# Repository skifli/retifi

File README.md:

# Retifi

- [Retifi](#retifi)
  - [Journal](#journal)
  - [PCB](#pcb)
    - [Schematic](#schematic)
    - [PCB Design](#pcb-design)
  - [BOM](#bom)

A simple reaction time tester consisting of a main module, and two handheld parts (with a push-button each), and a lil screen (the blank area will be covered by various stickers from different Hackclub YSWSs I have participate in - mainly Sprig lol).

I made this because I compete in a competition called F1 in Schools (although its now been rebranded to STEM Racing, supported by F1), and as part of the competition our reaction times play a big role when launching the miniature F1 in Schools car down the track (side note you should totally check us out, we won the uk national finals last year in dev class, and are competing this year after exams - https://instagram.com/warp_racing_ and https://warp-racing.com).

Also sorry for this being a tad rushed with the images etc, I just lost a bunch of time because of GitHub Codespace being a pain ()

## Journal

Can be found in [`JOURNAL.md`](JOURNAL.md).

> [!NOTE]\
> Total time spent: **27h**

## PCB

### Schematic

### PCB Design

## BOM

In USD, $62.52.

<details closed>
<summary> Click to open (closed by default to save space lol)</summary>

| Component                | Description      | Notes                                                                                | Quantity | Price      | Shipping             | Provider               | Link                                                                                  |
| ------------------------ | ---------------- | ------------------------------------------------------------------------------------ | -------- | ---------- | -------------------- | ---------------------- | ------------------------------------------------------------------------------------- |
| Headers                  |                  | For screen because it doesn’t specify coming with some and I am taking zilch chances | 1        | £1.08      |                      | AliExpress             | [Link](https://www.aliexpress.com/item/4000988113226.html)                            |
| JST PH 2.00mm            | PH 2.00mm        | To connect the buttons to the PCB                                                    | 1        | £2.25      |                      |                        | [Link](https://www.aliexpress.com/item/1005007691949301.html)                         |
| Momentary Push Button    | Red 5PCS         | The actual button                                                                    | 1        | £3.23      |                      |                        | [Link](https://www.aliexpress.com/item/1005008498887267.html)                         |
| Heat Shrink Tube         | Mixed size       | Heat around the joint for the button to the switch                                   | 1        | £1.35      |                      |                        | [Link](https://www.aliexpress.com/item/1005008146302901.html)                         |
| Slide Switch             | k014a004-G3      | Switching it up here, eh? Lol ok that’s enough bad jokes for a day ;-;               | 1        | £2.09      |                      |                        | [Link](https://www.aliexpress.com/item/1005008904067609.html)                         |
| Nice nano                | But cheaaaper    | Teeheehee                                                                            | 1        | £2.21      |                      |                        | [Link](https://www.aliexpress.com/item/1005007383270623.html)                         |
| OLED                     | 2.42 I2C         |                                                                                      | 1        | £9.79      |                      |                        | [Link](https://www.aliexpress.com/item/1005008741364067.html)                         |
| Micro JST                | Male 5 Pcs 100mm | [Adafruit Guide](https://learn.adafruit.com/on-slash-off-switches/overview)          | 1        | £0.50      | £1.97                |                        | [Link](https://www.aliexpress.com/item/1005008864177105.html)                         |
| Micro JST                | Male 5 Pcs 100mm | [Adafruit Guide](https://learn.adafruit.com/on-slash-off-switches/overview)          | 1        | £0.34      | £1.97                |                        | [Link](https://www.aliexpress.com/item/1005008864177105.html)                         |
| Push Button              | 6x6x6mm          | For the reset function                                                               | 1        | £0.74      | £2.16                |                        | [Link](https://www.aliexpress.com/item/4001224103835.html)                            |
| **Total (AliExpress)**   |                  |                                                                                      |          | **£29.68** | Included on ze left! |                        |                                                                                       |
|                          |                  |                                                                                      |          |            |                      |                        |                                                                                       |
| 150mAh 3.7V LiPo Battery |                  | Couldn’t find any shipping sooner from AliExpress.                                   | 1        | £4.50      | £3.90                | PiHut                  | [Link](https://thepihut.com/products/150mah-3-7v-lipo-battery?variant=42388690993347) |
| **Total (PiHut)**        |                  |                                                                                      |          | **£8.40**  |                      |                        |                                                                                       |
|                          |                  |                                                                                      |          |            |                      |                        |                                                                                       |
| Comus Neodynium Magnet   | 3 by 4mm         | Again, AliExpress shipping is atrocious on this front.                               | 1        | £2.18      | £3.30 + £1.10 (VAT)  | Rapid Electronics (UK) | [Link](https://www.rapidonline.com/comus-m1219-3-neodynium-disc-magnet-78-1068)       |
|                          |                  |                                                                                      |          | **£6.58**  |                      |                        |                                                                                       |
|                          |                  |                                                                                      |          |            |                      |                        |                                                                                       |
| PCB                      |                  |                                                                                      | 1        | £1.51      | £1.13                | JLCPCB                 |                                                                                       |
|                          |                  |                                                                                      |          | **£2.64**  |                      |                        |                                                                                       |
|                          |                  |                                                                                      |          |            |                      |                        |                                                                                       |
| **TOTAL**                |                  |                                                                                      |          | **£47.30** |                      |                        |                                                                                       |

</details>

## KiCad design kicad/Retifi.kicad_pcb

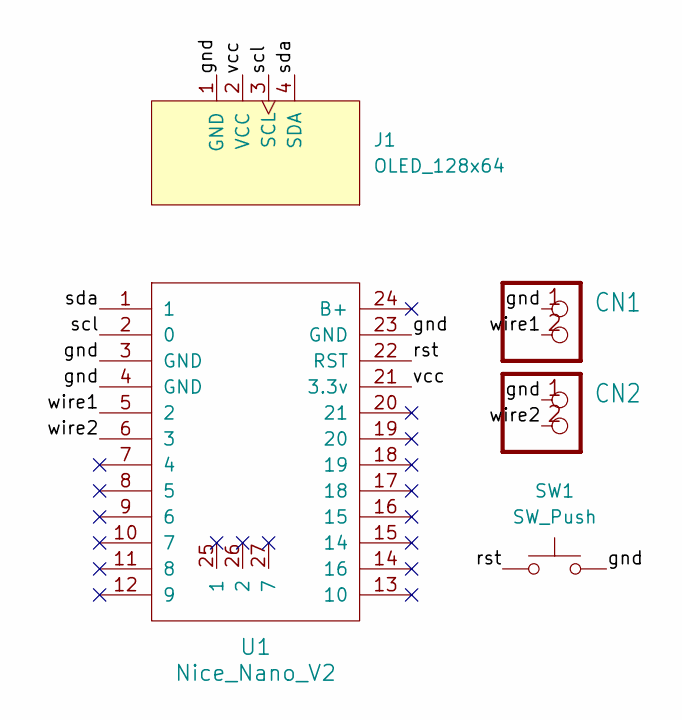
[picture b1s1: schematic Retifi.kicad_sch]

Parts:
CN1, CN2: JST_PH_S2B-PH-SM4-TB_1x02-1MP_P2.00mm_Horizontal
J1: OLED_128x64
SW1: SW_Push; Generic 2 Pin Horizontal
U1: Nice_Nano_V2

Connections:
/gnd: CN1.1, CN2.1, J1.1 (GND), SW1.2, U1.3 (GND), U1.4 (GND), U1.23 (GND)
/rst: SW1.1, U1.22 (RST)
/scl: J1.3 (SCL), U1.2 (0)
/sda: J1.4 (SDA), U1.1
/vcc: J1.2 (VCC), U1.21 (3.3v)
/wire1: CN1.2, U1.5 (2)
/wire2: CN2.2, U1.6 (3)

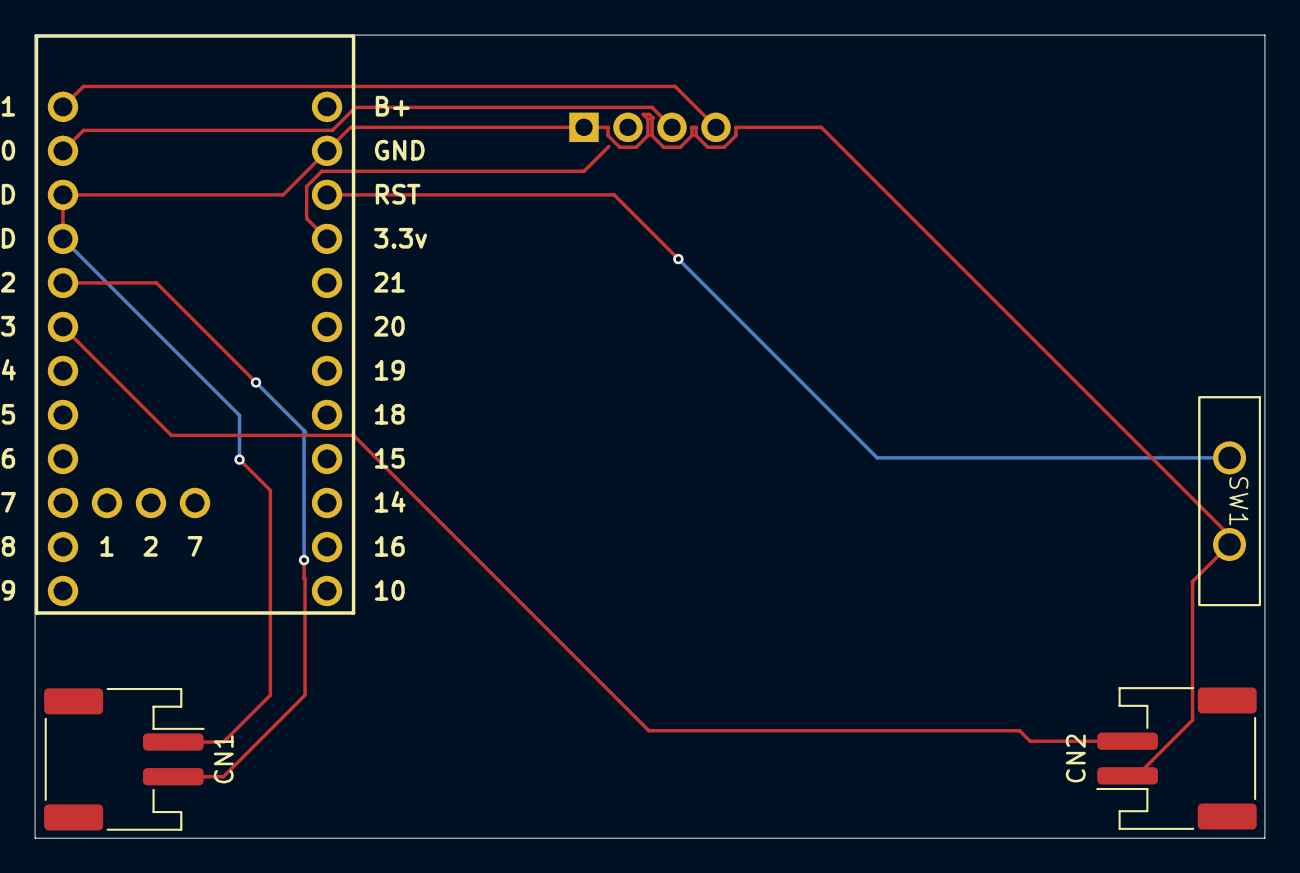
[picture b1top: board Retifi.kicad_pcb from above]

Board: 2 copper layers, 71.0 x 46.4 mm, 5 parts (0 on the bottom side), 7 nets.

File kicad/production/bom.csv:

Designator,Footprint,Quantity,Value,LCSC Part #
"CN1, CN2",JST_PH_S2B-PH-SM4-TB_1x02-1MP_P2.00mm_Horizontal,2,~,
J1,OLED_128x64,1,OLED_128x64,
SW1,Generic 2 Pin Horizontal,1,SW_Push,
U1,Nice_Nano_V2,1,Nice_Nano_V2,

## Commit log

2025-07-31 feat: upload files because codespaces is gone ;-;
2025-07-31 fix: typo
2025-07-31 fix: upload kicad
